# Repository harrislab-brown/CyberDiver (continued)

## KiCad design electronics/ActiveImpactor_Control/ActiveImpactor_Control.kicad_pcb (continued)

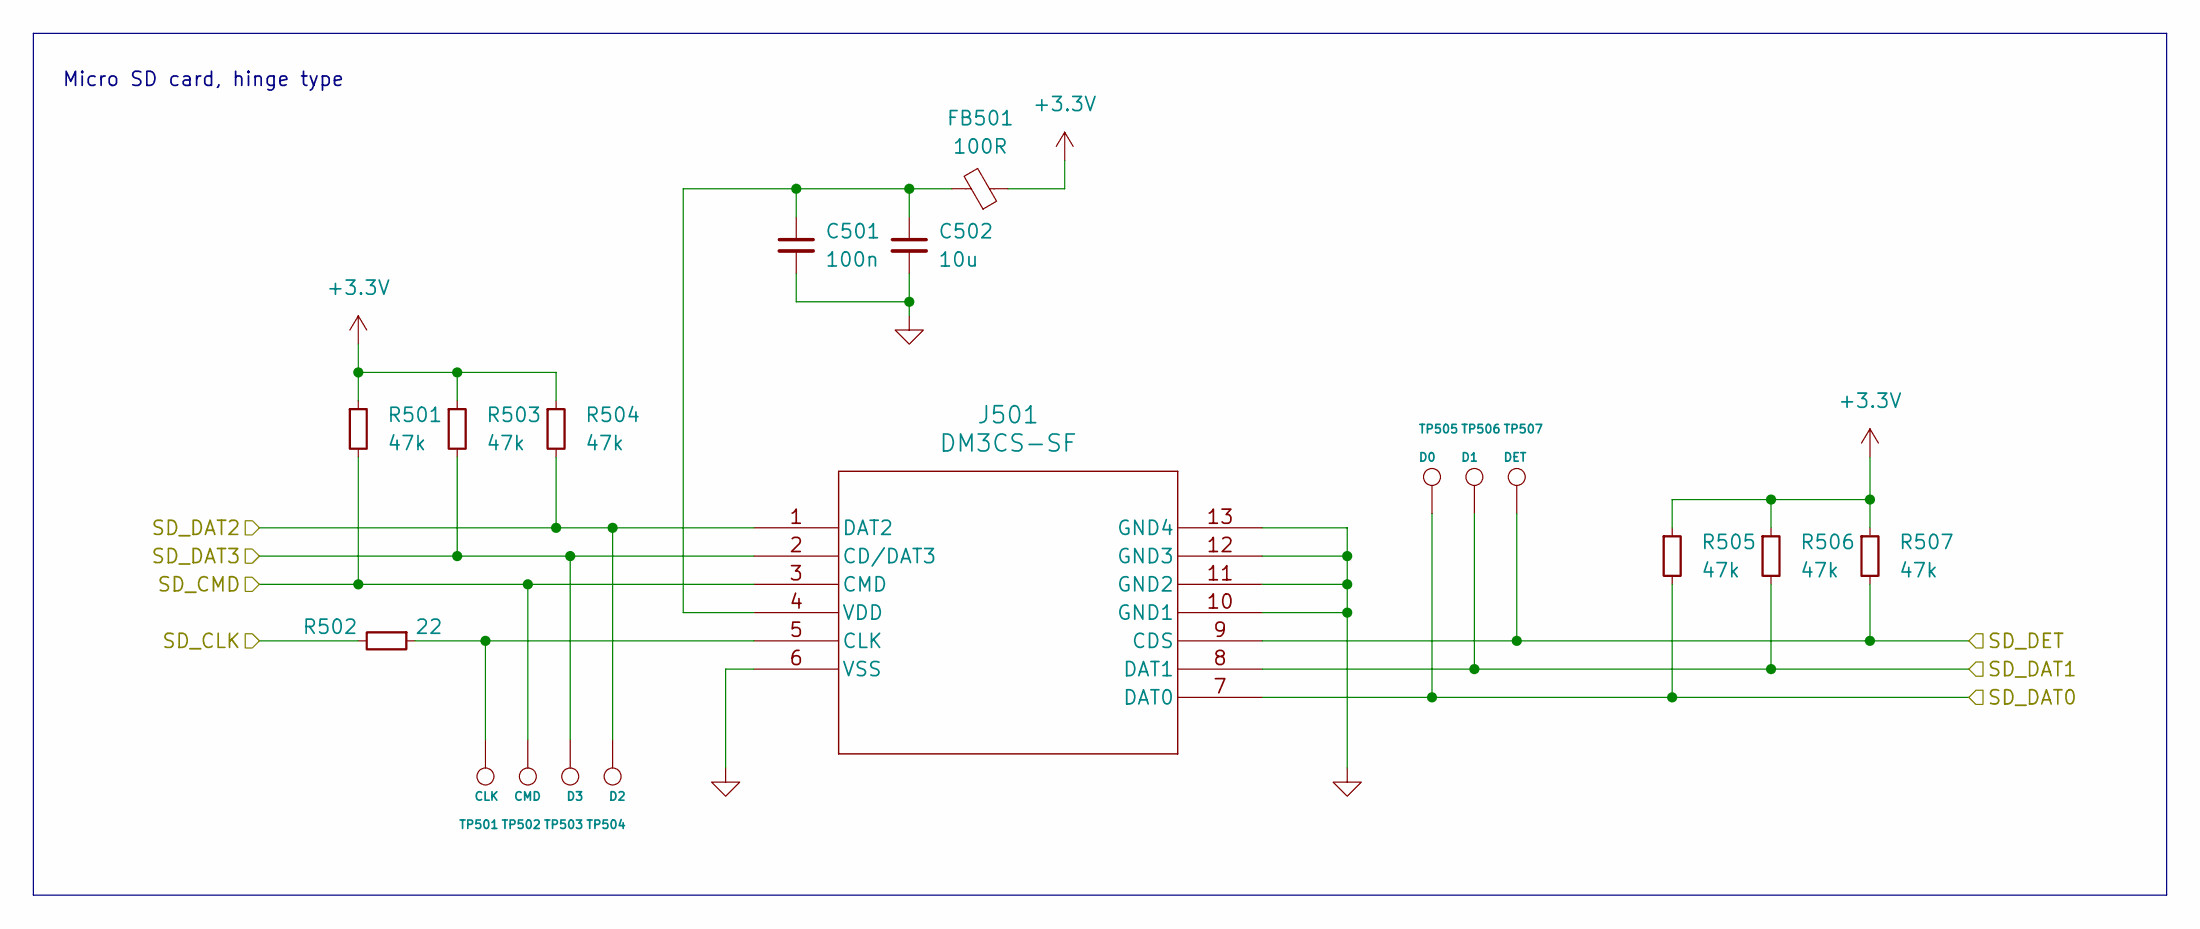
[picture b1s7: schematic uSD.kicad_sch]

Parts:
C501: 100n; C_0402_1005Metric; LCSC C1525
C502: 10u; C_0603_1608Metric; LCSC C19702
FB501: 100R; L_0603_1608Metric; LCSC C1002
J501: DM3CS-SF; DM3CS-SF_HIR; LCSC C202111
R501, R503, R504, R505, R506, R507: 47k; R_0402_1005Metric; LCSC C25792
R502: 22; R_0402_1005Metric; LCSC C25092
TP501: CLK; TestPoint_Pad_D1.0mm
TP502: CMD; TestPoint_Pad_D1.0mm
TP503: D3; TestPoint_Pad_D1.0mm
TP504: D2; TestPoint_Pad_D1.0mm
TP505: D0; TestPoint_Pad_D1.0mm
TP506: D1; TestPoint_Pad_D1.0mm
TP507: DET; TestPoint_Pad_D1.0mm

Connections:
+3.3V: FB501.1, R501.1, R503.1, R504.1, R505.1, R506.1, R507.1; also elsewhere on the board
/microcontroller/SDMMC1_CK: R502.2; also elsewhere on the board
/microcontroller/SDMMC1_CMD: J501.3 (CMD), R501.2, TP502.1; also elsewhere on the board
/microcontroller/SDMMC1_D0: J501.7 (DAT0), R505.2, TP505.1; also elsewhere on the board
/microcontroller/SDMMC1_D1: J501.8 (DAT1), R506.2, TP506.1; also elsewhere on the board
/microcontroller/SDMMC1_D2: J501.1 (DAT2), R504.2, TP504.1; also elsewhere on the board
/microcontroller/SDMMC1_D3: J501.2 (CD/DAT3), R503.2, TP503.1; also elsewhere on the board
/microcontroller/SD_DET: J501.9 (CDS), R507.2, TP507.1; also elsewhere on the board
GND: C501.2, C502.2, J501.6 (VSS), J501.10 (GND1), J501.11 (GND2), J501.12 (GND3), J501.13 (GND4); also elsewhere on the board
unnamed: J501.5 (CLK), R502.1, TP501.1
unnamed: C501.1, C502.1, FB501.2, J501.4 (VDD)

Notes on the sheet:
Micro SD card, hinge type

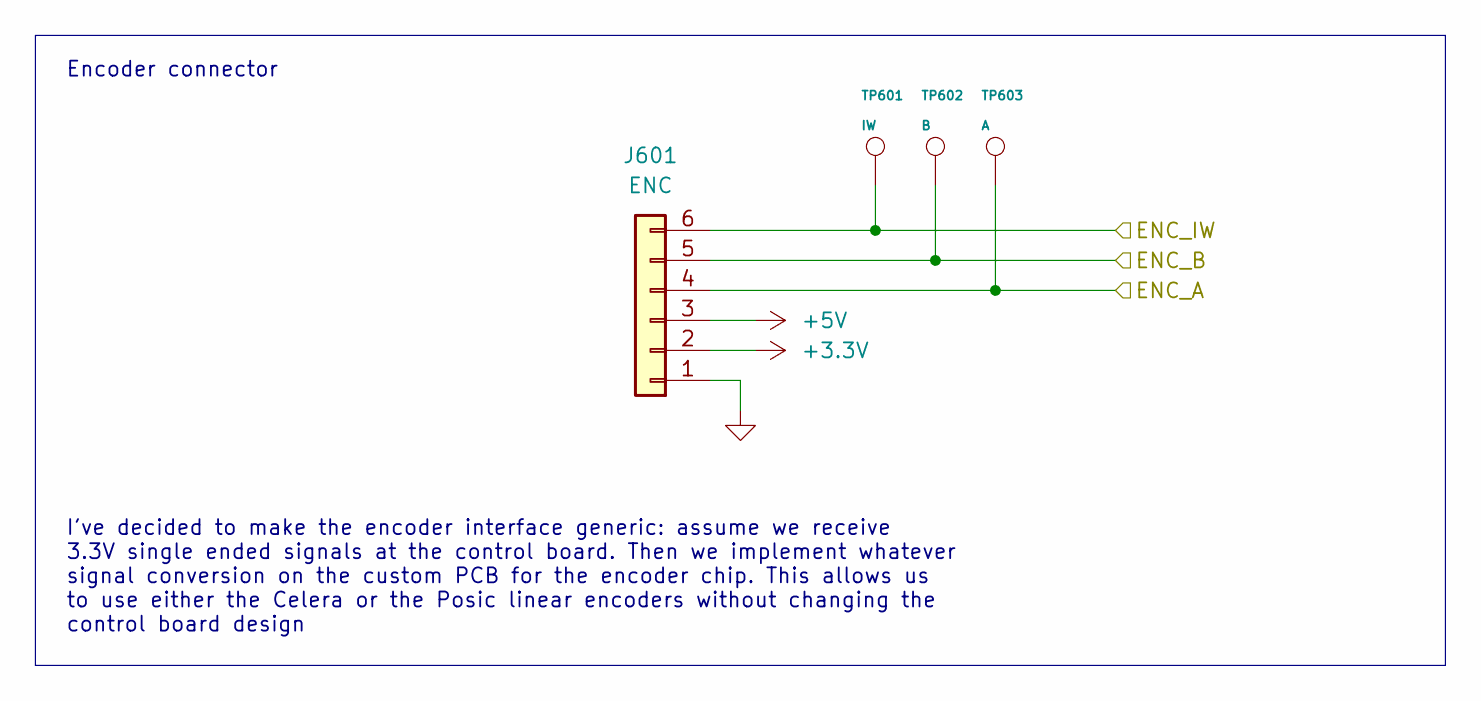
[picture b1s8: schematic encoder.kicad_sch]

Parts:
J601: ENC; JST_SH_SM06B-SRSS-TB_1x06-1MP_P1.00mm_Horizontal; LCSC C160405
TP601: IW; TestPoint_Pad_D1.0mm
TP602: B; TestPoint_Pad_D1.0mm
TP603: A; TestPoint_Pad_D1.0mm

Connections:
+3.3V: J601.2; also elsewhere on the board
+5V: J601.3; also elsewhere on the board
/encoder/ENC_A: J601.4, TP603.1; also elsewhere on the board
/encoder/ENC_B: J601.5, TP602.1; also elsewhere on the board
/encoder/ENC_IW: J601.6, TP601.1; also elsewhere on the board
GND: J601.1; also elsewhere on the board

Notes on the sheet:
Encoder connector
I've decided to make the encoder interface generic: assume we receive 3.3V single ended signals at the control board. Then we implement whatever signal conversion on the custom PCB for the encoder chip. This allows us to use either the Celera or the Posic linear encoders without changing the contro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

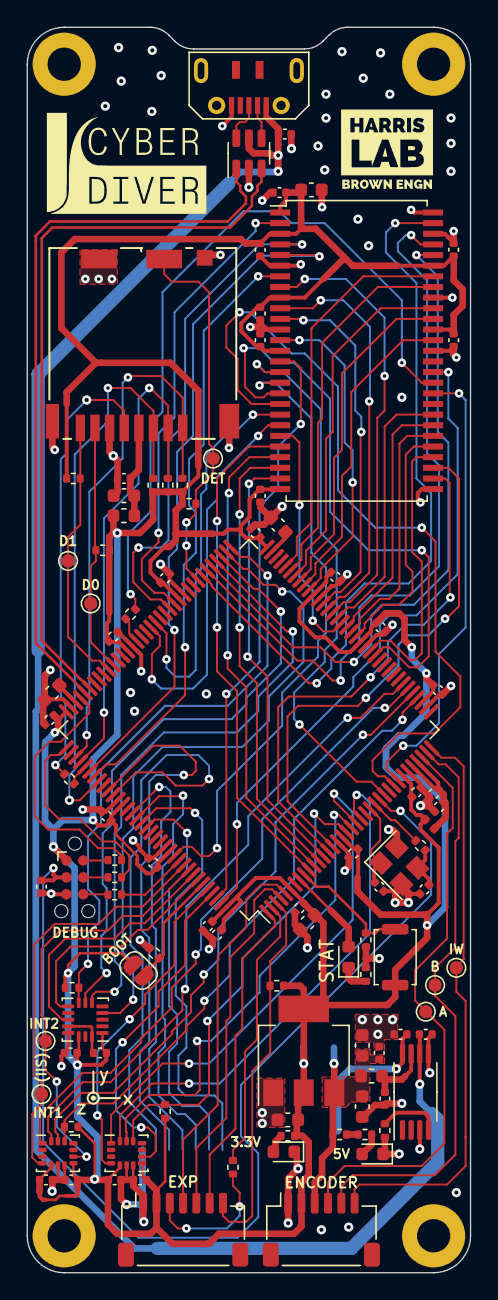
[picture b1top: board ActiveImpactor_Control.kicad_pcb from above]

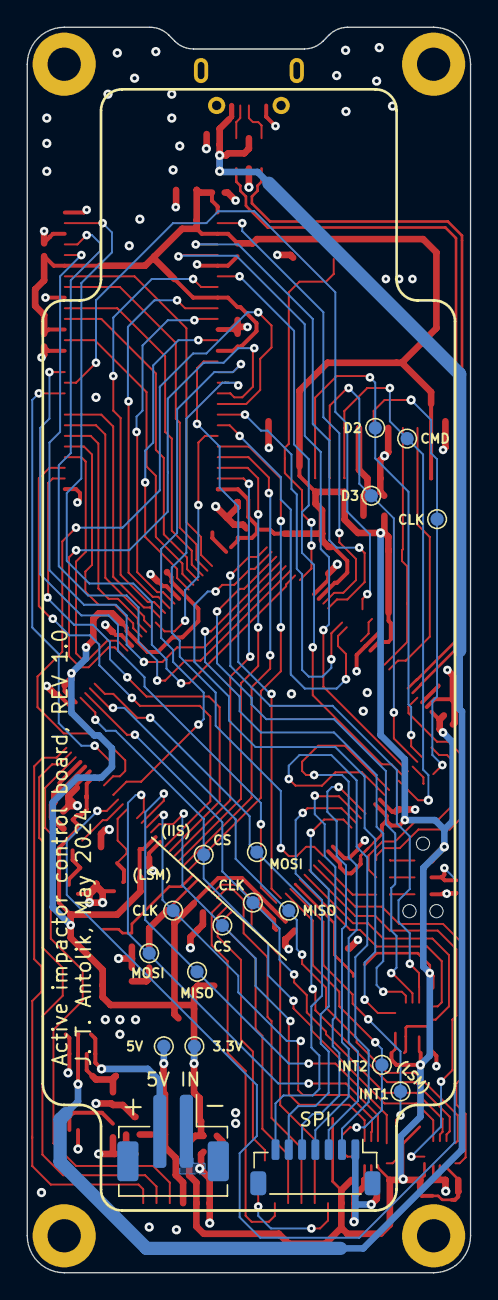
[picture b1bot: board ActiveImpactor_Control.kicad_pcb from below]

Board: 4 copper layers, 33.3 x 93.7 mm, 122 parts (18 on the bottom side), 112 nets.

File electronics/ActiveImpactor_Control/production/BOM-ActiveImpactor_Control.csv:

Comment,Designator,Footprint,LCSC
100R,"FB101,FB501",L_0603_1608Metric,C1002
1k,"R101,R102,R103,R104,R204",R_0402_1005Metric,C11702
10n,C219,C_0402_1005Metric,C15195
100n,"C101,C102,C103,C105,C202,C204,C205,C207,C208,C209,C210,C211,C212,C213,C214,C215,C216,C217,C221,C301,C402,C403,C404,C405,C406,C407,C408,C501,C701,C702,C703,C704,C705,C706",C_0402_1005Metric,C1525
12p,"C203,C206",C_0402_1005Metric,C1547
ENC,J601,JST_SH_SM06B-SRSS-TB_1x06-1MP_P1.00mm_Horizontal,C160405
EXP,J801,JST_SH_SM07B-SRSS-TB_1x07-1MP_P1.00mm_Horizontal,C160406
10u,"C104,C201,C401,C502",C_0603_1608Metric,C19702
DM3CS-SF,J501,DM3CS-SF_HIR,C202111
BUTTON,SW201,SW_Push_SPST_NO_Alps_SKRK,C202388
2u2,"C220,C222",C_0603_1608Metric,C23630
22,"R205,R206,R207,R401,R502,R802",R_0402_1005Metric,C25092
47,R202,R_0402_1005Metric,C25118
10k,"R201,R203",R_0402_1005Metric,C25744
47k,"R501,R503,R504,R505,R506,R507,R701,R702,R703,R801",R_0402_1005Metric,C25792
39n,L201,L_0402_1005Metric,C26443
22u,"C106,C107",C_0603_1608Metric,C2762594
USBLC6-2SC6,U301,SOT-23-6,C2827654
ADXL373,U702,Analog_LGA-16_3.25x3mm_P0.5mm_LayoutBorder3x5y,C3216386
USB_B_Micro,J301,MicroXNJ,C404969
1u,C218,C_0402_1005Metric,C52923
AMS1117-3.3,U102,SOT-223-3_TabPin2,C6186
W9812G6KH-6,U401,TSOP-II-54_22.2x10.16mm_P0.8mm,C62379
TPS2115APWR,U101,TSSOP-8_4.4x3mm_P0.65mm,C70287
24MHz,Y201,Crystal_SMD_3225-4Pin_3.2x2.5mm,C70590
IIS3DWBTR,U703,LGA-14_3x2.5mm_P0.5mm_LayoutBorder3x4y,C717702
STM32H723ZGTx,U201,LQFP-144_20x20mm_P0.5mm,C730146
STAT,D201,LED_0603_1608Metric,C84266
LED_5V,"D101,D102",LED_0603_1608Metric,C965805
LSM6DS3TR-C,U701,LGA-14_3x2.5mm_P0.5mm_LayoutBorder3x4y,C967633

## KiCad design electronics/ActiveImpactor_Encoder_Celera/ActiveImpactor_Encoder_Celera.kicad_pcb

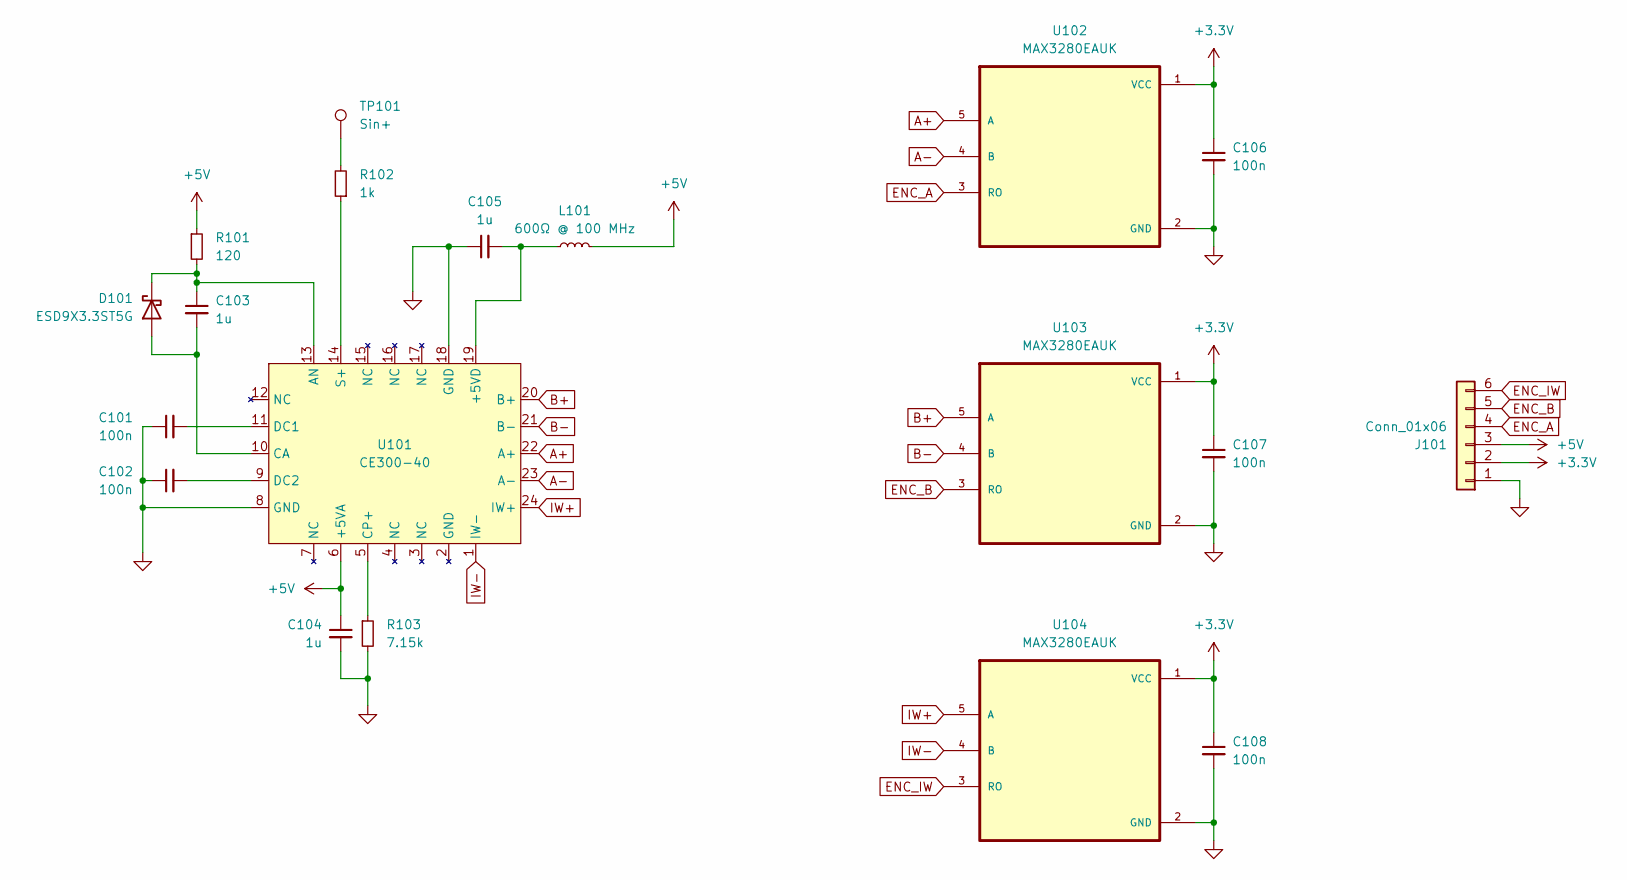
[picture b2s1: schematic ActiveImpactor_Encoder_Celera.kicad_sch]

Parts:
C101, C102, C106, C107, C108: 100n; C_0402_1005Metric; LCSC C1525
C103, C104, C105: 1u; C_0603_1608Metric; LCSC C15849
D101: ESD9X3.3ST5G; D_SOD-923; LCSC C130456
J101: Conn_01x06; JST_SH_BM06B-SRSS-TB_1x06-1MP_P1.00mm_Vertical; LCSC C160392
L101: 600Ω @ 100 MHz; L_0603_1608Metric; LCSC C19330
R101: 120; R_0402_1005Metric; LCSC C25079
R102: 1k; R_0402_1005Metric; LCSC C11702
R103: 7.15k; R_0402_1005Metric; LCSC C270586
TP101: Sin+; TestPoint_Pad_D1.5mm
U101: CE300-40
U102, U103, U104: MAX3280EAUK; SOT-23-5; LCSC C131126

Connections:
+3.3V: C106.1, C107.1, C108.1, J101.2, U102.1 (VCC), U103.1 (VCC), U104.1 (VCC)
+5V: C104.1, J101.3, L101.2, R101.1, U101.6 (+5VA)
A+: U101.22 (A+), U102.5 (A)
A-: U101.23 (A-), U102.4 (B)
B+: U101.20 (B+), U103.5 (A)
B-: U101.21 (B-), U103.4 (B)
ENC_A: J101.4, U102.3 (RO)
ENC_B: J101.5, U103.3 (RO)
ENC_IW: J101.6, U104.3 (RO)
GND: C101.1, C102.1, C104.2, C105.1, C106.2, C107.2, C108.2, J101.1, R103.2, U101.8 (GND), U101.18 (GND), U102.2 (GND), U103.2 (GND), U104.2 (GND)
IW+: U101.24 (IW+), U104.5 (A)
IW-: U101.1 (IW-), U104.4 (B)
unnamed: C103.2, D101.2 (A), U101.10 (CA)
unnamed: C103.1, D101.1 (K), R101.2, U101.13 (AN)
unnamed: R102.2, TP101.1
unnamed: C105.2, L101.1, U101.19 (+5VD)
unnamed: R103.1, U101.5 (CP+)
unnamed: C101.2, U101.11 (DC1)
unnamed: C102.2, U101.9 (DC2)
unnamed: R102.1, U101.14 (S+)

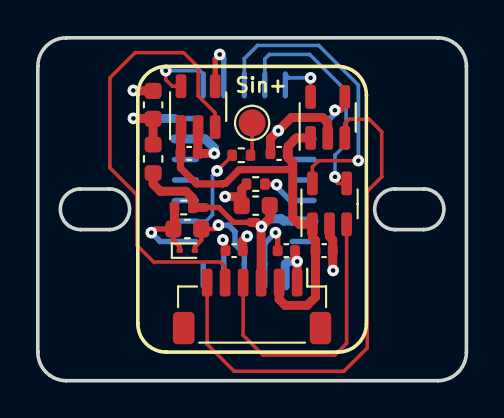
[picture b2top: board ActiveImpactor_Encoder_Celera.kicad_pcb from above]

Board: 4 copper layers, 23.8 x 19.1 mm, 19 parts (1 on the bottom side), 20 nets.

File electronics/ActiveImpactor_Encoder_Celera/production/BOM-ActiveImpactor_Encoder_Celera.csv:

Comment,Designator,Footprint,LCSC
1k,R102,R_0402_1005Metric,C11702
ESD9X3.3ST5G,D101,D_SOD-923,C130456
MAX3280EAUK,"U102,U103,U104",SOT-23-5,C131126
100n,"C101,C102,C106,C107,C108",C_0402_1005Metric,C1525
1u,"C103,C104,C105",C_0603_1608Metric,C15849
Conn_01x06,J101,JST_SH_BM06B-SRSS-TB_1x06-1MP_P1.00mm_Vertical,C160392
600Ω @ 100 MHz,L101,L_0603_1608Metric,C19330
120,R101,R_0402_1005Metric,C25079
7.15k,R103,R_0402_1005Metric,C270586

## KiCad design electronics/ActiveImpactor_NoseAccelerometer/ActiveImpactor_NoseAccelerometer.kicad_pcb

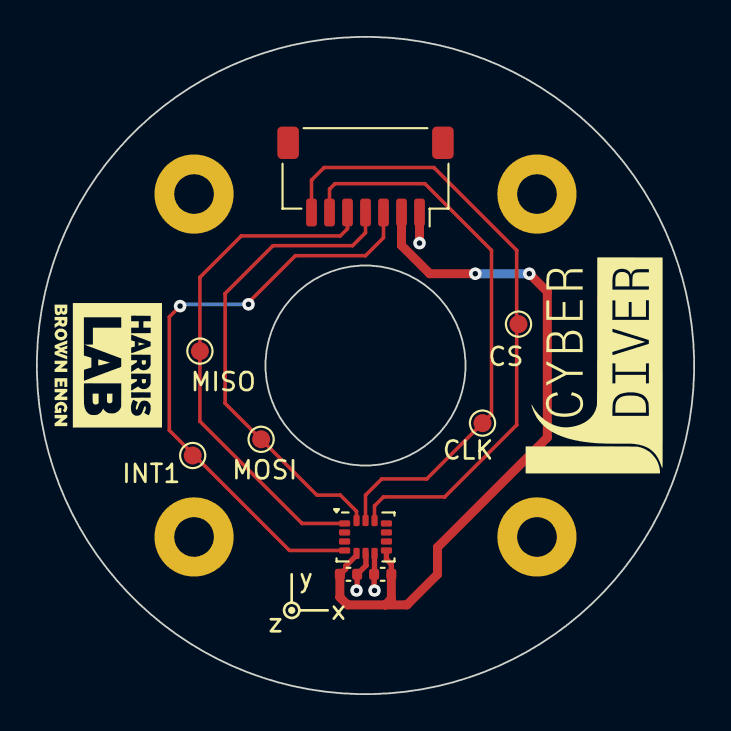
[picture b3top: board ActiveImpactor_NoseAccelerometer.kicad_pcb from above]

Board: 2 copper layers, 36.5 x 36.5 mm, 13 parts (0 on the bottom side), 7 nets.

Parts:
C101, C102: 100n; C_0402_1005Metric
CLK: CLK; TestPoint_Pad_D1.0mm
CS: CS; TestPoint_Pad_D1.0mm
H101, H102, H103, H104: MountingHole; MountingHole_2.2mm_M2_Pad
INT1: INT1; TestPoint_Pad_D1.0mm
J101: EXP; JST_SH_SM07B-SRSS-TB_1x07-1MP_P1.00mm_Horizontal
MISO: MISO; TestPoint_Pad_D1.0mm
MOSI: MOSI; TestPoint_Pad_D1.0mm
U101: LSM6DS3TR-C; LGA-14_3x2.5mm_P0.5mm_LayoutBorder3x4y

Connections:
+3.3V: C101.1, C102.1, J101.2, U101.5 (VDDIO), U101.8 (VDD)
/CLK: CLK.1, J101.6, U101.13 (SCL)
/CS: CS.1, J101.7, U101.12 (CS)
/INT: INT1.1, J101.3, U101.4 (INT1)
/MISO: J101.5, MISO.1, U101.1 (SDO/SA0)
/MOSI: J101.4, MOSI.1, U101.14 (SDA)
GND: C101.2, C102.2, J101.1, U101.6 (GND), U101.7 (GND)

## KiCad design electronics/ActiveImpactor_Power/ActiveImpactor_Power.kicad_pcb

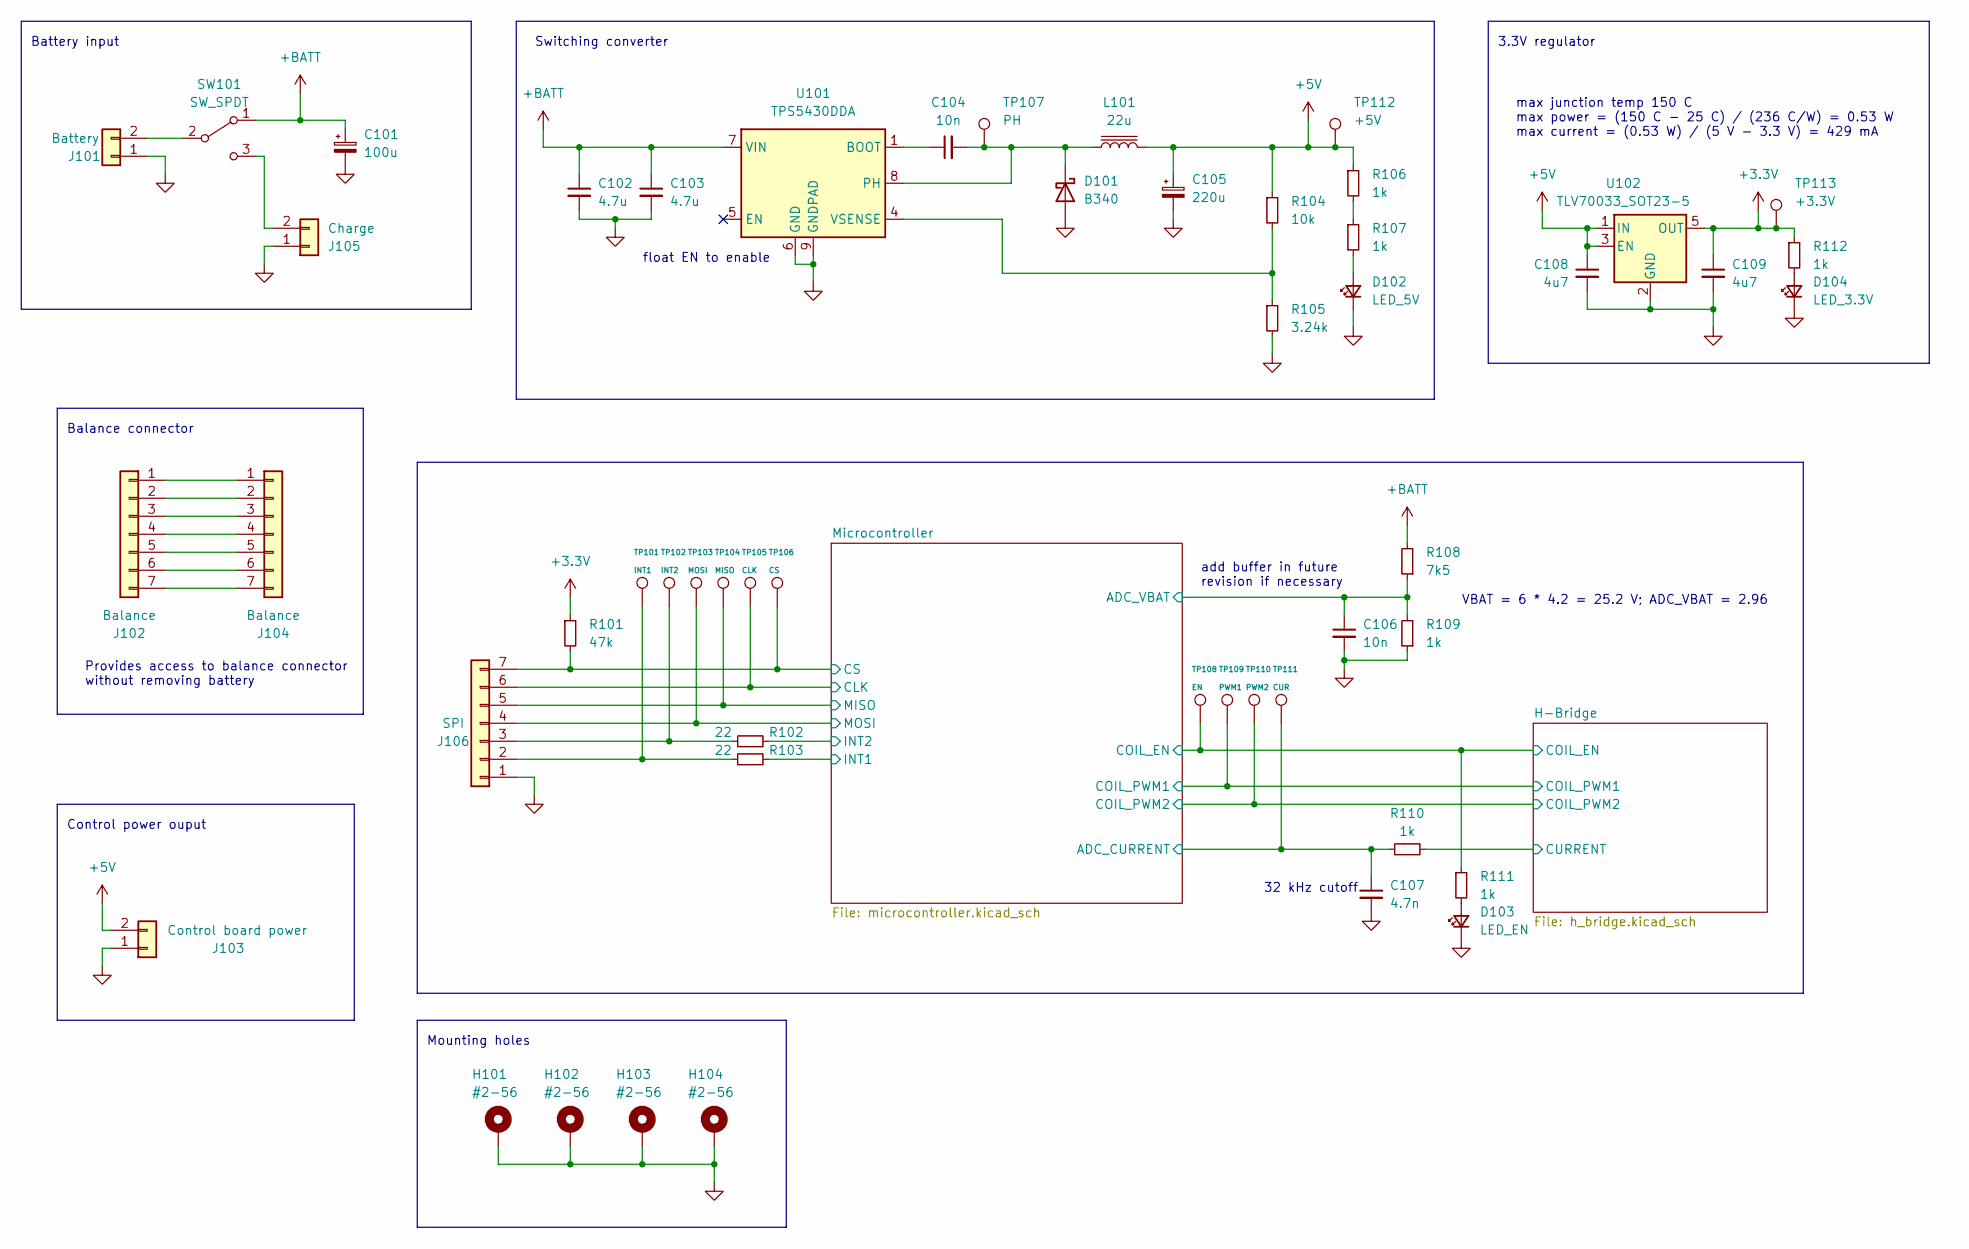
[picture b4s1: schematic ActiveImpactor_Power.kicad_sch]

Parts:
C101: 100u; CP_Elec_6.3x5.8; LCSC C128464
C102, C103: 4.7u; C_1206_3216Metric; LCSC C29823
C104: 10n; C_0603_1608Metric; LCSC C57112
C105: 220u; CP_EIA-7343-40_Kemet-Y; LCSC C242173
C106: 10n; C_0402_1005Metric; LCSC C15195
C107: 4.7n; C_0603_1608Metric; LCSC C53987
C108, C109: 4u7; C_0603_1608Metric; LCSC C19666
D101: B340; D_SMA; LCSC C64982
D102: LED_5V; LED_0603_1608Metric; LCSC C965805
D103: LED_EN; LED_0603_1608Metric; LCSC C2286
D104: LED_3.3V; LED_0603_1608Metric; LCSC C965805
H101, H102, H103, H104: #2-56; MountingHole_2.5mm_Pad
J101: Battery; AMASS_XT30U-M_1x02_P5.0mm_Vertical
J102: Balance; JST_XH_B7B-XH-A_1x07_P2.50mm_Vertical; Digikey 455-B7B-XH-A-ND
J103: Control board power; JST_PH_B2B-PH-SM4-TB_1x02-1MP_P2.00mm_Vertical; Digikey 455-B2B-PH-SM4-TBCT-ND
J104: Balance; JST_SH_SM07B-SRSS-TB_1x07-1MP_P1.00mm_Horizontal; LCSC C160406
J105: Charge; JST_PH_S2B-PH-SM4-TB_1x02-1MP_P2.00mm_Horizontal; LCSC C295747
J106: SPI; JST_SH_BM07B-SRSS-TB_1x07-1MP_P1.00mm_Vertical; Digikey 455-BM07B-SRSS-TBCT-ND
L101: 22u; L_Sunlord_MWSA0603S; LCSC C408453
R101: 47k; R_0402_1005Metric; LCSC C25792
R102, R103: 22; R_0402_1005Metric; LCSC C25092
R104: 10k; R_0603_1608Metric; LCSC C25804
R105: 3.24k; R_0603_1608Metric; LCSC C22994
R106, R107, R110, R112: 1k; R_0603_1608Metric; LCSC C21190
R108: 7k5; R_0402_1005Metric; LCSC C137934
R109, R111: 1k; R_0402_1005Metric; LCSC C11702
SW101: SW_SPDT; SW_500SSP1S1M6QEA; Digikey EG2478-ND
TP101: INT1; TestPoint_Pad_D1.0mm
TP102: INT2; TestPoint_Pad_D1.0mm
TP103: MOSI; TestPoint_Pad_D1.0mm
TP104: MISO; TestPoint_Pad_D1.0mm
TP105: CLK; TestPoint_Pad_D1.0mm
TP106: CS; TestPoint_Pad_D1.0mm
TP107: PH; TestPoint_Pad_D1.0mm
TP108: EN; TestPoint_Pad_D1.0mm
TP109: PWM1; TestPoint_Pad_D1.0mm
TP110: PWM2; TestPoint_Pad_D1.0mm
TP111: CUR; TestPoint_Pad_D1.0mm
TP112: +5V; TestPoint_Pad_D1.0mm
TP113: +3.3V; TestPoint_Pad_D1.0mm
U101: TPS5430DDA; TI_SO-PowerPAD-8_ThermalVias; LCSC C9864
U102: TLV70033_SOT23-5; SOT-23-5; LCSC C11337

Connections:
+3.3V: C109.1, R101.1, R112.1, TP113.1, U102.5 (OUT); also elsewhere on the board
+5V: C105.1, C108.1, J103.2, L101.2, R104.1, R106.1, TP112.1, U102.1 (IN), U102.3 (EN)
+BATT: C101.1, C102.1, C103.1, R108.2, SW101.1 (A), U101.7 (VIN); also elsewhere on the board
/H-Bridge/COIL_EN: R111.1, TP108.1; also elsewhere on the board
/H-Bridge/COIL_PWM1: TP109.1; also elsewhere on the board
/H-Bridge/COIL_PWM2: TP110.1; also elsewhere on the board
/H-Bridge/CURRENT: R110.2; also elsewhere on the board
/Microcontroller/ADC_CURRENT: C107.1, R110.1, TP111.1; also elsewhere on the board
/Microcontroller/ADC_VBAT: C106.1, R108.1, R109.2; also elsewhere on the board
/Microcontroller/CLK: J106.6, TP105.1; also elsewhere on the board
/Microcontroller/CS: J106.7, R101.2, TP106.1; also elsewhere on the board
/Microcontroller/INT1: R103.2; also elsewhere on the board
/Microcontroller/INT2: R102.2; also elsewhere on the board
/Microcontroller/MISO: J106.5, TP104.1; also elsewhere on the board
/Microcontroller/MOSI: J106.4, TP103.1; also elsewhere on the board
GND: C101.2, C102.2, C103.2, C105.2, C106.2, C107.2, C108.2, C109.2, D101.2 (A), D102.1 (K), D103.1 (K), D104.1 (K), H101.1, H102.1, H103.1, H104.1, J101.1, J103.1, J105.1, J106.1, R105.2, R109.1, U101.6 (GND), U101.9 (GNDPAD), U102.2 (GND); also elsewhere on the board
unnamed: C104.2, D101.1 (K), L101.1, TP107.1, U101.8 (PH)
unnamed: D102.2 (A), R107.2
unnamed: D103.2 (A), R111.2
unnamed: D104.2 (A), R112.2
unnamed: J101.2, SW101.2 (B)
unnamed: J102.1, J104.1
unnamed: J102.2, J104.2
unnamed: J102.3, J104.3
unnamed: J102.4, J104.4
unnamed: J102.5, J104.5
unnamed: J102.6, J104.6
unnamed: J102.7, J104.7
unnamed: J105.2, SW101.3 (C)
unnamed: J106.2, R103.1, TP101.1
unnamed: J106.3, R102.1, TP102.1
unnamed: R106.2, R107.1
unnamed: C104.1, U101.1 (BOOT)
unnamed: R104.2, R105.1, U101.4 (VSENSE)

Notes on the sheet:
Balance connector
VBAT = 6 * 4.2 = 25.2 V; ADC_VBAT = 2.96
Battery input
Mounting holes
Switching converter
32 kHz cutoff
Control power ouput
add buffer in future revision if necessary
max junction temp 150 C max power = (150 C - 25 C) / (236 C/W) = 0.53 W max current = (0.53 W) / (5 V - 3.3 V) = 429 mA
float EN to enable
3.3V regulator
Provides access to balance connector without removing battery

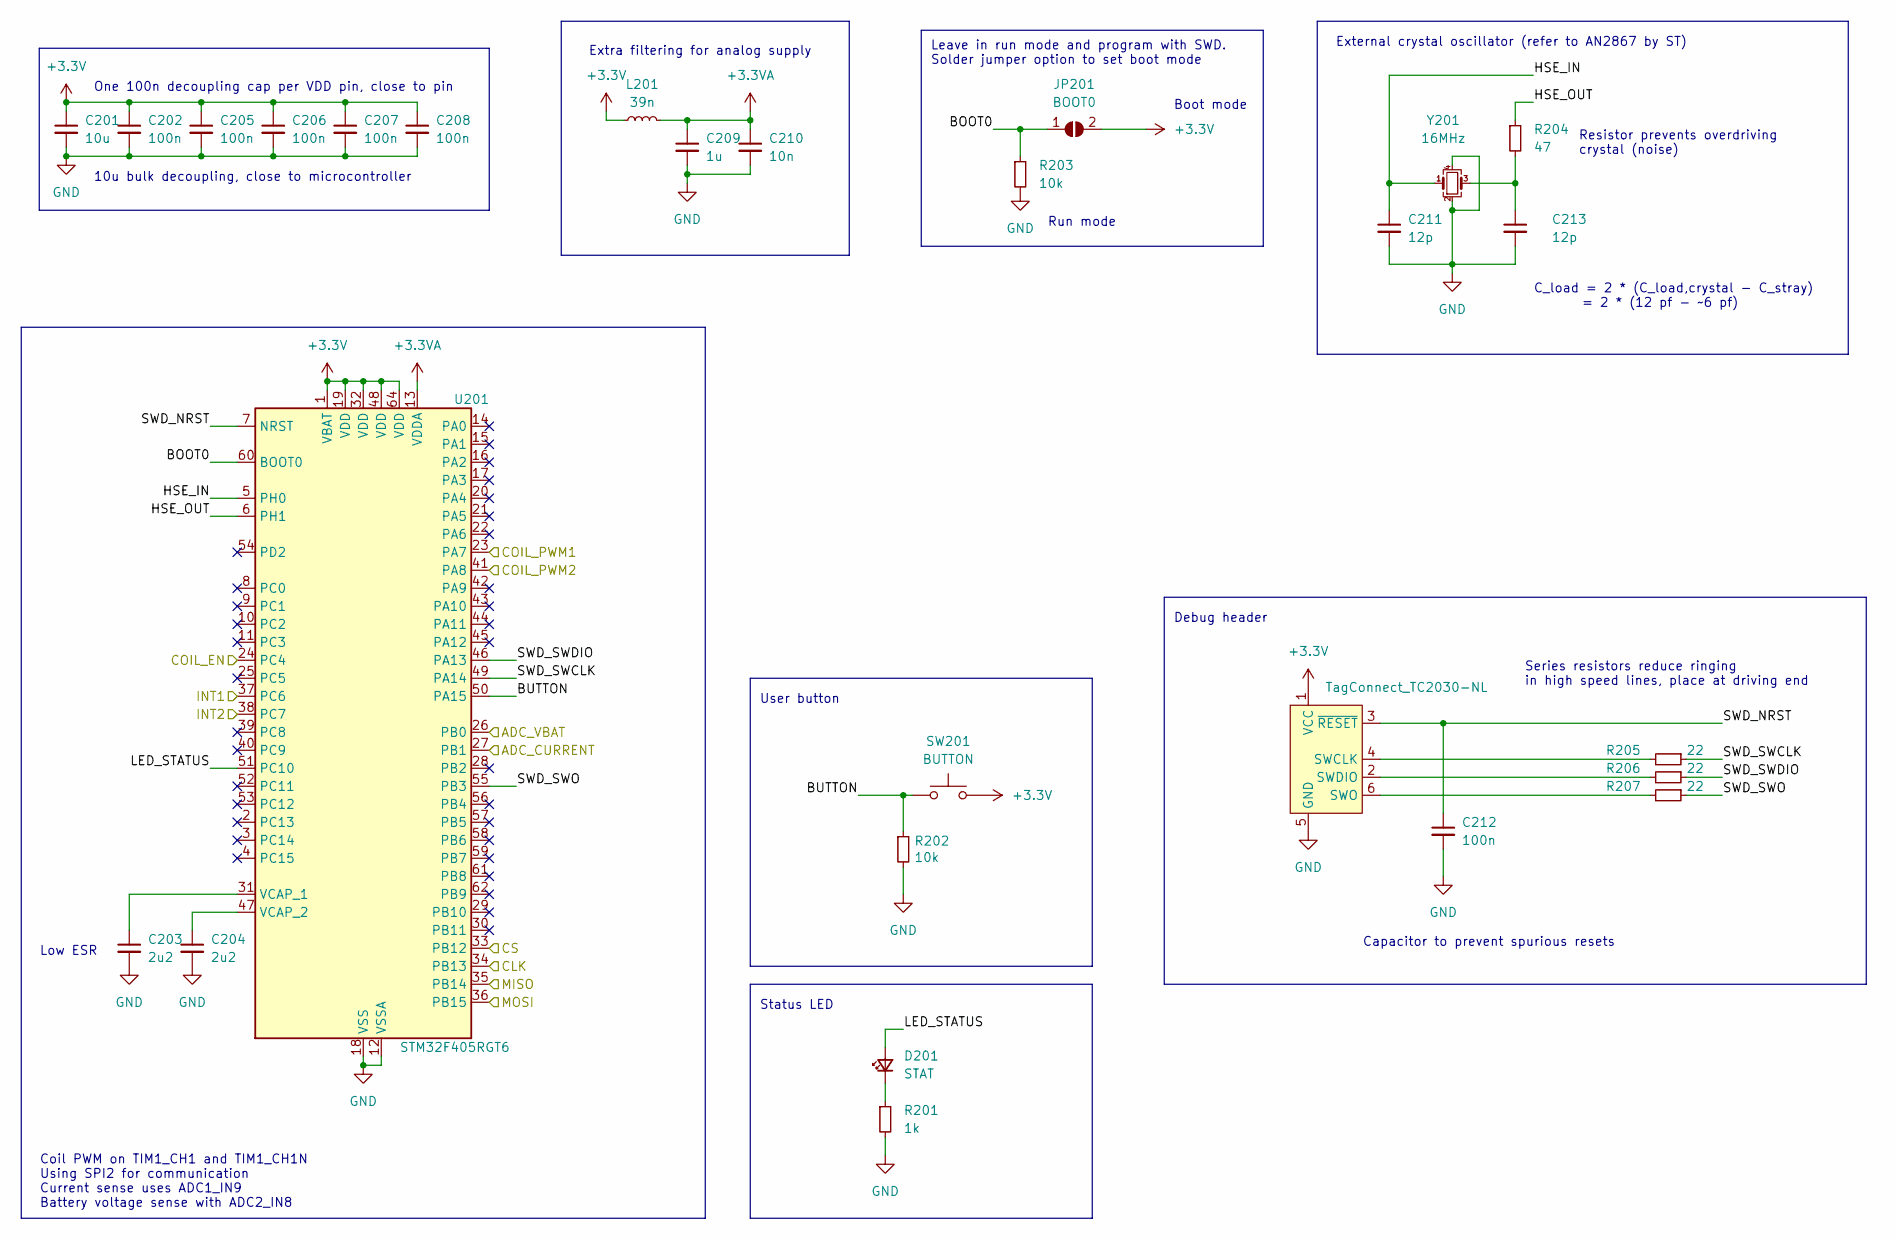
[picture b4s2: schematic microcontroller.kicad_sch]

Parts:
C201: 10u; C_0603_1608Metric; LCSC C19702
C202, C205, C206, C207, C208, C212: 100n; C_0402_1005Metric; LCSC C1525
C203, C204: 2u2; C_0603_1608Metric; LCSC C23630
C209: 1u; C_0402_1005Metric; LCSC C52923
C210: 10n; C_0402_1005Metric; LCSC C15195
C211, C213: 12p; C_0402_1005Metric; LCSC C1547
D201: STAT; LED_0603_1608Metric; LCSC C84266
J201: TagConnect_TC2030-NL; Tag-Connect_TC2030-IDC-NL_2x03_P1.27mm_Vertical
JP201: BOOT0; SolderJumper-2_P1.3mm_Open_RoundedPad1.0x1.5mm
L201: 39n; L_0402_1005Metric; LCSC C26443
R201: 1k; R_0402_1005Metric; LCSC C11702
R202, R203: 10k; R_0402_1005Metric; LCSC C25744
R204: 47; R_0402_1005Metric; LCSC C25118
R205, R206, R207: 22; R_0402_1005Metric; LCSC C25092
SW201: BUTTON; SW_Push_SPST_NO_Alps_SKRK; LCSC C202388
U201: STM32F405RGT6; LQFP-64_10x10mm_P0.5mm; LCSC C15742
Y201: 16MHz; Crystal_SMD_3225-4Pin_3.2x2.5mm; LCSC C13738

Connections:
+3.3V: C201.1, C202.1, C205.1, C206.1, C207.1, C208.1, J201.1 (VCC), JP201.2 (B), L201.1, SW201.2, U201.1 (VBAT), U201.19 (VDD), U201.32 (VDD), U201.48 (VDD), U201.64 (VDD); also elsewhere on the board
+3.3VA: C209.1, C210.1, L201.2, U201.13 (VDDA)
/H-Bridge/COIL_EN: U201.24 (PC4); also elsewhere on the board
/H-Bridge/COIL_PWM1: U201.23 (PA7); also elsewhere on the board
/H-Bridge/COIL_PWM2: U201.41 (PA8); also elsewhere on the board
/Microcontroller/ADC_CURRENT: U201.27 (PB1); also elsewhere on the board
/Microcontroller/ADC_VBAT: U201.26 (PB0); also elsewhere on the board
/Microcontroller/BOOT0: JP201.1 (A), R203.1, U201.60 (BOOT0)
/Microcontroller/BUTTON: R202.1, SW201.1, U201.50 (PA15)
/Microcontroller/CLK: U201.34 (PB13); also elsewhere on the board
/Microcontroller/CS: U201.33 (PB12); also elsewhere on the board
/Microcontroller/HSE_IN: C211.1, U201.5 (PH0), Y201.1
/Microcontroller/HSE_OUT: R204.1, U201.6 (PH1)
/Microcontroller/INT1: U201.37 (PC6); also elsewhere on the board
/Microcontroller/INT2: U201.38 (PC7); also elsewhere on the board
/Microcontroller/LED_STATUS: D201.2 (A), U201.51 (PC10)
/Microcontroller/MISO: U201.35 (PB14); also elsewhere on the board
/Microcontroller/MOSI: U201.36 (PB15); also elsewhere on the board
/Microcontroller/SWD_NRST: C212.1, J201.3 (~RESET), U201.7 (NRST)
/Microcontroller/SWD_SWCLK: R205.1, U201.49 (PA14)
/Microcontroller/SWD_SWDIO: R206.1, U201.46 (PA13)
/Microcontroller/SWD_SWO: R207.1, U201.55 (PB3)
GND: C201.2, C202.2, C203.2, C204.2, C205.2, C206.2, C207.2, C208.2, C209.2, C210.2, C211.2, C212.2, C213.2, J201.5 (GND), R201.2, R202.2, R203.2, U201.12 (VSSA), U201.18 (VSS), U201.63 (VSS), Y201.2, Y201.4; also elsewhere on the board
unnamed: C213.1, R204.2, Y201.3
unnamed: D201.1 (K), R201.1
unnamed: J201.4 (SWCLK), R205.2
unnamed: J201.2 (SWDIO), R206.2
unnamed: J201.6 (SWO), R207.2
unnamed: C203.1, U201.31 (VCAP_1)
unnamed: C204.1, U201.47 (VCAP_2)

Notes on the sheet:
C_load = 2 * (C_load,crystal - C_stray) = 2 * (12 pf - ~6 pf)
Debug header
Leave in run mode and program with SWD. Solder jumper option to set boot mode
User button
One 100n decoupling cap per VDD pin, close to pin
Low ESR
Boot mode
Status LED
Extra filtering for analog supply
Capacitor to prevent spurious resets
Run mode
10u bulk decoupling, close to microcontroller
External crystal oscillator (refer to AN2867 by ST)
Coil PWM on TIM1_CH1 and TIM1_CH1N Using SPI2 for communication Current sense uses ADC1_IN9 Battery voltage sense with ADC2_IN8
Series resistors reduce ringing in high speed lines, place at driving end
Resistor prevents overdriving crystal (noise)
